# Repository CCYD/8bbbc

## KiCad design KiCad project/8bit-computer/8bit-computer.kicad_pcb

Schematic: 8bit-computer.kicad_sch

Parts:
C1, C3, C5, C6, C7, C8, C9, C10, C11, C12, C13, C14, C15, C16, C17, C18, C19, C20, C21, C22, C23, C24, C25, C26, C27, C28, C29, C30, C31, C32, C33, C34, C35, C36, C37, C38, C39, C40, C41, C42, C43, C44, C45, C46, C47, C48, C51, C52, C53, C54, C55, C56, C57, C60, C61, C63, C64, C65, C66, C67, C68, C69, C70: 0.1uF; C_Disc_D5.0mm_W2.5mm_P5.00mm
C2, C4: 1uF; C_Disc_D5.0mm_W2.5mm_P5.00mm
C49, C50: .01u; C_Disc_D5.0mm_W2.5mm_P5.00mm
C58, C59: 4.7u; CP_Radial_D8.0mm_P2.50mm
C62: 1u; C_Disc_D5.0mm_W2.5mm_P5.00mm
D1, D2, D3, D4, D7, D8, D9, D10, D11, D12, D13, D14, D17, D18, D19, D20, D21, D22, D23, D24, D25, D29, D30, D31, D32, D33, D34, D35, D36, D37, D39, D40, D41, D42, D43, D44, D45, D46, D47, D48, D49, D50, D51, D52, D53, D54, D55, D56, D57, D58, D59, D60, D61, D62, D63, D64, D69, D70, D71, D72, D73, D74, D75, D76, D77, D78, D79, D80, D81, D82, D83, D84, D85, D86, D87, D88, D89, D90, D91, D92, D93: LED; LED_D5.0mm
D5: Green; LED_D5.0mm
D6: Red; LED_D5.0mm
D15: 5817; D_A-405_P7.62mm_Horizontal
D16, D65, D66, D67, D68: Yellow; LED_D5.0mm
D26, D27, D28, D38: LED; LED_D5.0mm; not fitted
H1, H2, H3, H4, H5, H6: MountingHole_Pad; MountingHole_2.7mm_M2.5_DIN965_Pad
IC1, IC2, IC3: AT28C16-15PI; DIP1550W56P254L3190H559Q24N; Mouser Part Number 556-AT28C16-15PI
J1: USB_C_Receptacle_PowerOnly_6P; USB_C_Receptacle_GCT_USB4085
JP1: Jumper_2_Open; PinHeader_1x02_P2.54mm_Vertical
R1, R5, R10, R31, R33, R36, R37, R59, R60, R61, R62, R63, R64, R65, R66, R85, R89, R90, R91, R95, R96: 1K; R_Axial_DIN0207_L6.3mm_D2.5mm_P10.16mm_Horizontal
R2, R3, R4, R9, R16, R17, R35: 10K; R_Axial_DIN0207_L6.3mm_D2.5mm_P10.16mm_Horizontal
R6: 470K; R_Axial_DIN0207_L6.3mm_D2.5mm_P10.16mm_Horizontal
R7, R8: 1M; R_Axial_DIN0207_L6.3mm_D2.5mm_P10.16mm_Horizontal
R15: 120R; R_Axial_DIN0207_L6.3mm_D2.5mm_P10.16mm_Horizontal
R18, R32, R94: R_Axial_DIN0207_L6.3mm_D2.5mm_P10.16mm_Horizontal
R34: R_US; R_Axial_DIN0207_L6.3mm_D2.5mm_P10.16mm_Horizontal
R50: 1K; R_Axial_DIN0207_L6.3mm_D2.5mm_P10.16mm_Horizontal; not fitted
R88: 20K; R_Axial_DIN0207_L6.3mm_D2.5mm_P10.16mm_Horizontal
R92, R93: 5.1K; R_Axial_DIN0207_L6.3mm_D2.5mm_P10.16mm_Horizontal
RN1, RN2, RN3, RN4, RN5, RN6, RN7, RN8, RN9, RN10, RN11: R_Network08_US; R_Array_SIP9
RN12, RN13, RN14, RN15: R_Network04_US; R_Array_SIP5
RV1: 1M; Potentiometer_Alpha_RD901F-40-00D_Single_Vertical_CircularH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
SW1, SW6, SW7: SW_Push; SW_PUSH-12mm
SW2: SW_DIP_x08; DIP-16_W7.62mm_LongPads
SW3: SW_DIP_x04; DIP-8_W7.62mm_LongPads
SW4, SW5, SW9: SW_DPDT_x2_Mine; SW_Push_2P2T_Toggle_CK_PVA2xxH1xxxxxxV2
U1, U2, U3, U52: NE555P; DIP-8_W7.62mm_Socket_LongPads
U4, U12, U13, U30, U31: 74LS04; DIP-14_W7.62mm_Socket_LongPads
U5, U45, U56: 74LS08; DIP-14_W7.62mm_Socket_LongPads
U6: 74LS32; DIP-14_W7.62mm_Socket_LongPads
U7, U25, U26, U35, U36, U37, U39, U46, U57, U58: 74LS173; DIP-16_W7.62mm_Socket_LongPads
U8, U9, U15, U16, U17, U18, U19: 74LS157; DIP-16_W7.62mm_Socket_LongPads
U10, U11: 74F189PC; DIP-16_W7.62mm_Socket_LongPads
U14, U27, U32, U34, U38, U47: 74LS245; DIP-20_W7.62mm_Socket_LongPads
U20, U21: 74LS595; DIP-16_W7.62mm_Socket_LongPads
U22: NodeMCU_v1.0
U23, U24: 74LS00; DIP-14_W7.62mm_Socket_LongPads
U28, U33: 74LS161; DIP-16_W7.62mm_Socket_LongPads
U29: 74LS138; DIP-16_W7.62mm_Socket_LongPads
U40, U41: 74LS283; DIP-16_W7.62mm_Socket_LongPads
U42, U43: 74LS86; DIP-14_W7.62mm_Socket_LongPads
U44: 74LS02; DIP-14_W7.62mm_Socket_LongPads
U48, U49, U50, U51: D168K; D1X8K
U53: 74LS107; DIP-14_W7.62mm_Socket_LongPads
U55: 74LS139; DIP-16_W7.62mm_Socket_LongPads

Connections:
/A: IC3.16 (I/O6), U48.7 (A), U49.7 (A), U50.7 (A), U51.7 (A)
/A0: D26.2 (A), IC1.8 (A0), IC2.8 (A0), U28.14 (Q0), U29.1 (A0)
/A1: D27.2 (A), IC1.7 (A1), IC2.7 (A1), U28.13 (Q1), U29.2 (A1)
/A2: D28.2 (A), IC1.6 (A2), IC2.6 (A2), U28.12 (Q2), U29.3 (A2)
/A4: D22.2 (A), IC1.5 (A3), IC2.5 (A3), U25.3 (Q0)
/A5: D23.2 (A), IC1.4 (A4), IC2.4 (A4), U25.4 (Q1)
/A6: D24.2 (A), IC1.3 (A5), IC2.3 (A5), U25.5 (Q2)
/A7: D25.2 (A), IC1.2 (A6), IC2.2 (A6), U25.6 (Q3)
/B: IC3.15 (I/O5), U48.6 (B), U49.6 (B), U50.6 (B), U51.6 (B)
/BUS_0: D70.2 (A), RN2.2 (R1), U7.14 (D0), U14.18 (B0), U18.2 (I0a), U26.14 (D0), U27.18 (B0), U32.2 (A0), U33.3 (D0), U34.18 (B0), U35.14 (D0), U37.14 (D0), U38.18 (B0), U47.18 (B0), U58.14 (D0)
/BUS_1: D71.2 (A), RN2.3 (R2), U7.13 (D1), U14.17 (B1), U18.5 (I0b), U26.13 (D1), U27.17 (B1), U32.3 (A1), U33.4 (D1), U34.17 (B1), U35.13 (D1), U37.13 (D1), U38.17 (B1), U47.17 (B1), U58.13 (D1)
/BUS_2: D72.2 (A), RN2.4 (R3), U7.12 (D2), U14.16 (B2), U18.11 (I0c), U26.12 (D2), U27.16 (B2), U32.4 (A2), U33.5 (D2), U34.16 (B2), U35.12 (D2), U37.12 (D2), U38.16 (B2), U47.16 (B2), U58.12 (D2)
/BUS_3: D73.2 (A), RN2.5 (R4), U7.11 (D3), U14.15 (B3), U18.14 (I0d), U26.11 (D3), U27.15 (B3), U32.5 (A3), U33.6 (D3), U34.15 (B3), U35.11 (D3), U37.11 (D3), U38.15 (B3), U47.15 (B3), U58.11 (D3)
/BUS_4: D74.2 (A), RN2.6 (R5), U14.14 (B4), U19.2 (I0a), U25.14 (D0), U27.14 (B4), U34.14 (B4), U36.14 (D0), U38.14 (B4), U39.14 (D0), U47.14 (B4), U57.14 (D0)
/BUS_5: D75.2 (A), RN2.7 (R6), U14.13 (B5), U19.5 (I0b), U25.13 (D1), U27.13 (B5), U34.13 (B5), U36.13 (D1), U38.13 (B5), U39.13 (D1), U47.13 (B5), U57.13 (D1)
/BUS_6: D76.2 (A), RN2.8 (R7), U14.12 (B6), U19.11 (I0c), U25.12 (D2), U27.12 (B6), U34.12 (B6), U36.12 (D2), U38.12 (B6), U39.12 (D2), U47.12 (B6), U57.12 (D2)
/BUS_7: D77.2 (A), RN2.9 (R8), U14.11 (B7), U19.14 (I0d), U25.11 (D3), U27.11 (B7), U34.11 (B7), U36.11 (D3), U38.11 (B7), U39.11 (D3), U47.11 (B7), U57.11 (D3)
/C: IC3.14 (I/O4), U48.4 (C), U49.4 (C), U50.4 (C), U51.4 (C)
/CARRY: U41.9 (C4), U46.14 (D0)
/D: IC3.13 (I/O3), U48.2 (D), U49.2 (D), U50.2 (D), U51.2 (D)
/DP: IC3.17 (I/O7), U48.5 (DP), U49.5 (DP), U50.5 (DP), U51.5 (DP)
/E: IC3.11 (I/O2), U48.1 (E), U49.1 (E), U50.1 (E), U51.1 (E)
/F: IC3.9 (I/O0), U48.9 (F), U49.9 (F), U50.9 (F), U51.9 (F)
/G: IC3.10 (I/O1), U48.10 (G), U49.10 (G), U50.10 (G), U51.10 (G)
/IR_A0: D18.2 (A), U26.3 (Q0), U27.2 (A0)
/IR_A1: D19.2 (A), U26.4 (Q1), U27.3 (A1)
/IR_A2: D20.2 (A), U26.5 (Q2), U27.4 (A2)
/IR_A3: D21.2 (A), U26.6 (Q3), U27.5 (A3)
/ZERO: U45.8, U46.13 (D1)
/a0: D65.2 (A), RN13.3 (R2), U9.4 (Za), U10.1 (A0), U11.1 (A0)
/a1: D66.2 (A), RN13.2 (R1), U9.7 (Zb), U10.15 (A1), U11.15 (A1)
/a2: D67.2 (A), RN13.5 (R4), U9.9 (Zc), U10.14 (A2), U11.14 (A2)
/a3: D68.2 (A), RN13.4 (R3), U9.12 (Zd), U10.13 (A3), U11.13 (A3)
/a_d0: D49.2 (A), U34.2 (A0), U35.3 (Q0), U40.5 (A1)
/a_d1: D50.2 (A), U34.3 (A1), U35.4 (Q1), U40.3 (A2)
/a_d2: D51.2 (A), U34.4 (A2), U35.5 (Q2), U40.14 (A3)
/a_d3: D52.2 (A), U34.5 (A3), U35.6 (Q3), U40.12 (A4)
/a_d4: D53.2 (A), U34.6 (A4), U36.3 (Q0), U41.5 (A1)
/a_d5: D54.2 (A), U34.7 (A5), U36.4 (Q1), U41.3 (A2)
/a_d6: D55.2 (A), U34.8 (A6), U36.5 (Q2), U41.14 (A3)
/a_d7: D56.2 (A), U34.9 (A7), U36.6 (Q3), U41.12 (A4)
/b_d0: D57.2 (A), U37.3 (Q0), U38.2 (A0), U42.2
/b_d1: D58.2 (A), U37.4 (Q1), U38.3 (A1), U42.5
/b_d2: D59.2 (A), U37.5 (Q2), U38.4 (A2), U42.10
/b_d3: D60.2 (A), U37.6 (Q3), U38.5 (A3), U42.13
/b_d4: D61.2 (A), U38.6 (A4), U39.3 (Q0), U43.2
/b_d5: D62.2 (A), U38.7 (A5), U39.4 (Q1), U43.5
/b_d6: D63.2 (A), U38.8 (A6), U39.5 (Q2), U43.10
/b_d7: D64.2 (A), U38.9 (A7), U39.6 (Q3), U43.13
/d0: U10.4 (D0), U16.4 (Za)
/d1: U10.6 (D1), U16.7 (Zb)
/d2: U10.10 (D2), U16.9 (Zc)
/d3: U10.12 (D3), U16.12 (Zd)
/d4: U11.4 (D0), U17.4 (Za)
/d5: U11.6 (D1), U17.7 (Zb)
/d6: U11.10 (D2), U17.9 (Zc)
/d7: U11.12 (D3), U17.12 (Zd)
ARD_HALT: R10.2, U6.4, U22.20 (D8)
ARD_MAR_INP_SEL: R31.2, U9.1 (S), U22.22 (D6)
ARD_MA_A0: U9.3 (I1a), U21.3 (QD)
ARD_MA_A1: U9.6 (I1b), U21.2 (QC)
ARD_MA_A2: U9.10 (I1c), U21.1 (QB)
ARD_MA_A3: U9.13 (I1d), U21.15 (QA)
ARD_RAM_D0: U16.3 (I1a), U20.7 (QH)
ARD_RAM_D1: U16.6 (I1b), U20.6 (QG)
ARD_RAM_D2: U16.10 (I1c), U20.5 (QF)
ARD_RAM_D3: U16.13 (I1d), U20.4 (QE)
ARD_RAM_D4: U17.3 (I1a), U20.3 (QD)
ARD_RAM_D5: U17.6 (I1b), U20.2 (QC)
ARD_RAM_D6: U17.10 (I1c), U20.1 (QB)
ARD_RAM_D7: U17.13 (I1d), U20.15 (QA)
ARD_RAM_INP_SEL: D16.2 (A), R34.2, U16.1 (S), U17.1 (S), U22.21 (D7)
ARD_RAM_WR_EN: R18.1, U10.3 (*WE), U11.3 (*WE), U15.12 (Zd), U22.27 (D3)
ARD_RESET: R36.1, SW7.2, U22.23 (D5), U23.12, U23.13
CLK: D4.2 (A), U4.13, U5.8, U7.7 (Cp), U24.12, U24.13, U25.7 (Cp), U26.7 (Cp), U33.2 (CP), U35.7 (Cp), U36.7 (Cp), U37.7 (Cp), U39.7 (Cp), U46.7 (Cp), U56.1
GND: C1.2, C2.2, C3.2, C4.2, C5.2, C6.2, C7.1, C8.1, C9.1, C10.1, C11.1, C12.1, C13.1, C14.1, C15.1, C16.1, C17.1, C18.1, C19.1, C21.1, C22.1, C23.1, C24.1, C25.1, C26.1, C27.1, C28.1, C29.1, C30.1, C31.1, C32.2, C33.2, C34.1, C35.1, C36.1, C37.1, C38.1, C39.1, C40.1, C41.1, C42.1, C43.1, C44.1, C45.1, C46.1, C47.1, C48.1, C49.2, C50.2, C51.1, C52.2, C53.2, C54.1, C55.1, C56.1, C57.2, C58.2, C59.2, C60.1, C61.2, C62.2, C63.1, C64.1, C65.1, C66.1, C67.1, C68.1, C69.1, C70.1, H1.1, H2.1, H3.1, H4.1, H5.1, H6.1, IC1.1 (A7), IC1.12 (GND), IC1.18 (~CE), IC1.19 (A10), IC1.20 (~OE), IC2.12 (GND), IC2.18 (~CE), IC2.19 (A10), IC2.20 (~OE), IC3.12 (GND), IC3.18 (~CE), IC3.20 (~OE), J1.A12 (GND), J1.B12 (GND), J1.S1 (SHIELD), R2.2, R3.2, R4.1, R9.2, R10.1, R31.1, R33.2, R34.1, R35.2, R36.2, R37.2, R50.2, R65.2, R66.2, R89.2, R92.1, R93.1, R94.1, R95.2, RN2.1 (common), RN3.1 (common), RN4.1 (common), RN5.1 (common), RN6.1 (common), RN7.1 (common), RN8.1 (common), RN9.1 (common), RN10.1 (common), RN11.1 (common), RN13.1 (common), RN14.1 (common), RN15.1 (common), RV1.MP (MountPin), SW1.1, SW2.1, SW2.2, SW2.3, SW2.4, SW2.5, SW2.6, SW2.7, SW2.8, SW3.1, SW3.2, SW3.3, SW3.4, SW4.1 (A), SW5.1 (A), SW6.1, SW9.2 (C), U1.1 (GND), U2.1 (GND), U3.1 (GND), U3.6 (THR), U4.7 (GND), U5.7 (GND), U6.7 (GND), U7.1 (Oe1), U7.2 (Oe2), U7.8 (GND), U8.8 (GND), U8.15 (E), U9.8 (GND), U9.15 (E), U10.2 (*CS), U10.8 (GND), U11.2 (*CS), U11.8 (GND), U12.7 (GND), U13.7 (GND), U14.10 (GND), U15.8 (GND), U15.15 (E), U16.8 (GND), U16.15 (E), U17.8 (GND), U17.15 (E), U18.8 (GND), U18.15 (E), U19.8 (GND), U19.15 (E), U20.8 (GND), U21.8 (GND), U22.10 (GND), U22.14 (GND), U22.17 (GND), U22.24 (GND), U23.7 (GND), U24.7 (GND), U25.1 (Oe1), U25.2 (Oe2), U25.8 (GND), U26.1 (Oe1), U26.2 (Oe2), U26.8 (GND), U27.6 (A4), U27.7 (A5), U27.8 (A6), U27.9 (A7), U27.10 (GND), U28.8 (GND), U29.4 (E1), U29.5 (E2), U29.8 (GND), U30.7 (GND), U31.7 (GND), U32.1 (A->B), U32.10 (GND), U33.8 (GND), U34.10 (GND), U35.1 (Oe1), U35.2 (Oe2), U35.8 (GND), U36.1 (Oe1), U36.2 (Oe2), U36.8 (GND), U37.1 (Oe1), U37.2 (Oe2), U37.8 (GND), U38.10 (GND), U39.1 (Oe1), U39.2 (Oe2), U39.8 (GND), U40.8 (GND), U41.8 (GND), U42.7 (GND), U43.7 (GND), U44.7 (GND), U45.7 (GND), U46.1 (Oe1), U46.2 (Oe2), U46.8 (GND), U46.11 (D3), U46.12 (D2), U47.10 (GND), U52.1 (GND), U53.7 (GND), U55.1 (E), U55.8 (GND), U56.7 (GND), U57.1 (Oe1), U57.2 (Oe2), U57.8 (GND), U57.9 (E1), U57.10 (E2), U58.1 (Oe1), U58.2 (Oe2), U58.8 (GND), U58.9 (E1), U58.10 (E2)
HALT: D78.2 (A), IC1.17 (I/O7), U6.5
JC_FLAG: D47.2 (A), IC1.23 (A8), IC2.23 (A8), U46.3 (Q0)
JZ_FLAG: D48.2 (A), IC1.22 (A9), IC2.22 (A9), U46.4 (Q1)
unnamed: C20.1, R37.1, U24.1
unnamed: C20.2, U24.8
unnamed: D1.2 (A), U1.3 (Q), U5.2
unnamed: D1.1 (K), R2.1
unnamed: D2.2 (A), U2.3 (Q), U5.5
unnamed: D2.1 (K), R3.1
unnamed: D3.2 (A), R8.2, U3.3 (Q), U4.1, U5.1
unnamed: D3.1 (K), R4.2
unnamed: D4.1 (K), R9.1
unnamed: D5.2 (A), R16.2
unnamed: D5.1 (K), SW4.3 (B)
unnamed: D6.2 (A), R17.2
unnamed: D6.1 (K), R15.2, SW4.2 (C), U8.1 (S), U15.1 (S), U24.4, U24.5
unnamed: D7.2 (A), U12.2, U14.2 (A0)
unnamed: D7.1 (K), RN5.2 (R1)
unnamed: D8.2 (A), U12.4, U14.3 (A1)
unnamed: D8.1 (K), RN5.3 (R2)
unnamed: D9.2 (A), U12.6, U14.4 (A2)
unnamed: D9.1 (K), RN5.4 (R3)
unnamed: D10.2 (A), U12.8, U14.5 (A3)
unnamed: D10.1 (K), RN5.5 (R4)
unnamed: D11.2 (A), U12.10, U14.6 (A4)
unnamed: D11.1 (K), RN5.6 (R5)
unnamed: D12.2 (A), U12.12, U14.7 (A5)
unnamed: D12.1 (K), RN5.7 (R6)
unnamed: D13.2 (A), U13.2, U14.8 (A6)
unnamed: D13.1 (K), RN5.8 (R7)
unnamed: D14.2 (A), U13.4, U14.9 (A7)
unnamed: D14.1 (K), RN5.9 (R8)
unnamed: D15.1 (K), U22.15 (VIN)
unnamed: D16.1 (K), R33.1
unnamed: D17.2 (A), U4.9, U6.6
unnamed: D17.1 (K), R35.1
unnamed: D18.1 (K), RN3.2 (R1)
unnamed: D19.1 (K), RN3.3 (R2)
unnamed: D20.1 (K), RN3.4 (R3)
unnamed: D21.1 (K), RN3.5 (R4)
unnamed: D22.1 (K), RN3.6 (R5)
unnamed: D23.1 (K), RN3.7 (R6)
unnamed: D24.1 (K), RN3.8 (R7)
unnamed: D25.1 (K), RN3.9 (R8)
unnamed: D26.1 (K), RN11.9 (R8)
unnamed: D27.1 (K), RN11.8 (R7)
unnamed: D28.1 (K), RN11.7 (R6)
unnamed: D29.2 (A), U29.15 (O0)
unnamed: D29.1 (K), RN11.2 (R1)
unnamed: D30.2 (A), U29.14 (O1)
unnamed: D30.1 (K), RN11.3 (R2)
unnamed: D31.2 (A), U29.13 (O2)
unnamed: D31.1 (K), RN11.4 (R3)
unnamed: D32.2 (A), U29.12 (O3)
unnamed: D32.1 (K), RN11.5 (R4)
unnamed: D33.2 (A), U29.11 (O4)
unnamed: D33.1 (K), RN11.6 (R5)
unnamed: D34.2 (A), U32.18 (B0), U33.14 (Q0)
unnamed: D34.1 (K), RN15.2 (R1)
unnamed: D35.2 (A), U32.17 (B1), U33.13 (Q1)
unnamed: D35.1 (K), RN15.3 (R2)
unnamed: D36.2 (A), U32.16 (B2), U33.12 (Q2)
unnamed: D36.1 (K), RN15.4 (R3)
unnamed: D37.2 (A), U32.15 (B3), U33.11 (Q3)
unnamed: D37.1 (K), RN15.5 (R4)
unnamed: D38.2 (A), U22.4 (SD3)
unnamed: D38.1 (K), R50.1
unnamed: D39.2 (A), U40.4 (S1), U44.12, U47.2 (A0)
unnamed: D39.1 (K), RN6.2 (R1)
unnamed: D40.2 (A), U40.1 (S2), U44.11, U47.3 (A1)
unnamed: D40.1 (K), RN6.3 (R2)
unnamed: D41.2 (A), U40.13 (S3), U44.9, U47.4 (A2)
unnamed: D41.1 (K), RN6.4 (R3)
unnamed: D42.2 (A), U40.10 (S4), U44.8, U47.5 (A3)
unnamed: D42.1 (K), RN6.5 (R4)
unnamed: D43.2 (A), U41.4 (S1), U44.6, U47.6 (A4)
unnamed: D43.1 (K), RN6.6 (R5)
unnamed: D44.2 (A), U41.1 (S2), U44.5, U47.7 (A5)
unnamed: D44.1 (K), RN6.7 (R6)
unnamed: D45.2 (A), U41.13 (S3), U44.3, U47.8 (A6)
unnamed: D45.1 (K), RN6.8 (R7)
unnamed: D46.2 (A), U41.10 (S4), U44.2, U47.9 (A7)
unnamed: D46.1 (K), RN6.9 (R8)
unnamed: D47.1 (K), R65.1
unnamed: D48.1 (K), R66.1
unnamed: D49.1 (K), RN8.2 (R1)
unnamed: D50.1 (K), RN8.3 (R2)
unnamed: D51.1 (K), RN8.4 (R3)
unnamed: D52.1 (K), RN8.5 (R4)
unnamed: D53.1 (K), RN8.6 (R5)
unnamed: D54.1 (K), RN8.7 (R6)
unnamed: D55.1 (K), RN8.8 (R7)
unnamed: D56.1 (K), RN8.9 (R8)
unnamed: D57.1 (K), RN7.2 (R1)
unnamed: D58.1 (K), RN7.3 (R2)
unnamed: D59.1 (K), RN7.4 (R3)
unnamed: D60.1 (K), RN7.5 (R4)
unnamed: D61.1 (K), RN7.6 (R5)
unnamed: D62.1 (K), RN7.7 (R6)
unnamed: D63.1 (K), RN7.8 (R7)
unnamed: D64.1 (K), RN7.9 (R8)
unnamed: D65.1 (K), RN14.5 (R4)
unnamed: D66.1 (K), RN14.4 (R3)
unnamed: D67.1 (K), RN14.3 (R2)
unnamed: D68.1 (K), RN14.2 (R1)
unnamed: D69.1 (K), R94.2
unnamed: D70.1 (K), RN4.2 (R1)
unnamed: D71.1 (K), RN4.3 (R2)
unnamed: D72.1 (K), RN4.4 (R3)
unnamed: D73.1 (K), RN4.5 (R4)
unnamed: D74.1 (K), RN4.6 (R5)
unnamed: D75.1 (K), RN4.7 (R6)
unnamed: D76.1 (K), RN4.8 (R7)
unnamed: D77.1 (K), RN4.9 (R8)
unnamed: D78.1 (K), RN9.2 (R1)
unnamed: D79.2 (A), IC1.16 (I/O6), U30.1
unnamed: D79.1 (K), RN9.3 (R2)
unnamed: D80.1 (K), RN9.4 (R3)
unnamed: D81.2 (A), IC1.14 (I/O4), U30.3
unnamed: D81.1 (K), RN9.5 (R4)
unnamed: D82.2 (A), IC1.13 (I/O3), U30.5
unnamed: D82.1 (K), RN9.6 (R5)
unnamed: D83.2 (A), IC1.11 (I/O2), U30.13
unnamed: D83.1 (K), RN9.7 (R6)
unnamed: D84.2 (A), IC1.9 (I/O0), U30.9
unnamed: D84.1 (K), RN9.8 (R7)
unnamed: D85.2 (A), IC1.10 (I/O1), U30.11
unnamed: D85.1 (K), RN9.9 (R8)
unnamed: D86.2 (A), IC2.17 (I/O7), U31.1
unnamed: D86.1 (K), RN10.2 (R1)
unnamed: D87.1 (K), RN10.3 (R2)
unnamed: D88.2 (A), IC2.15 (I/O5), U31.3
unnamed: D88.1 (K), RN10.4 (R3)
unnamed: D89.1 (K), RN10.5 (R4)
unnamed: D90.2 (A), IC2.11 (I/O2), U31.13
unnamed: D90.1 (K), RN10.6 (R5)
unnamed: D91.1 (K), RN10.7 (R6)
unnamed: D92.2 (A), IC2.10 (I/O1), U31.11
unnamed: D92.1 (K), RN10.8 (R7)
unnamed: D93.2 (A), IC2.9 (I/O0), U31.5
unnamed: D93.1 (K), RN10.9 (R8)
unnamed: IC3.8 (A0), U58.3 (Q0)
unnamed: IC3.7 (A1), U58.4 (Q1)
unnamed: IC3.6 (A2), U58.5 (Q2)
unnamed: IC3.5 (A3), U58.6 (Q3)
unnamed: IC3.4 (A4), U57.3 (Q0)
unnamed: IC3.3 (A5), U57.4 (Q1)
unnamed: IC3.2 (A6), U57.5 (Q2)
unnamed: IC3.1 (A7), U57.6 (Q3)
unnamed: IC3.23 (A8), U53.2 (~Q), U53.9 (C), U55.2 (A0)
unnamed: IC3.22 (A9), U53.5 (Q), U55.3 (A1)
unnamed: IC3.19 (A10), JP1.1 (A), R89.1
unnamed: J1.A5 (CC1), R93.2
unnamed: J1.B5 (CC2), R92.2
unnamed: R59.1, U45.12, U45.13
unnamed: R60.2, U5.12, U5.13
unnamed: R61.2, U4.3, U4.5, U4.11
unnamed: R62.2, U6.9, U6.10, U6.12, U6.13
unnamed: R63.1, U13.5, U13.9, U13.11, U13.13
unnamed: R64.1, U31.9
unnamed: R91.1, U56.4, U56.5, U56.9, U56.10, U56.12, U56.13
unnamed: R96.2, RV1.3
unnamed: RN1.2 (R1), SW2.16, U18.3 (I1a)
unnamed: RN1.3 (R2), SW2.15, U18.6 (I1b)
unnamed: RN1.4 (R3), SW2.14, U18.10 (I1c)
unnamed: RN1.5 (R4), SW2.13, U18.13 (I1d)
unnamed: RN1.6 (R5), SW2.12, U19.3 (I1a)
unnamed: RN1.7 (R6), SW2.11, U19.6 (I1b)
unnamed: RN1.8 (R7), SW2.10, U19.10 (I1c)
unnamed: RN1.9 (R8), SW2.9, U19.13 (I1d)
unnamed: RN12.2 (R1), SW3.8, U8.11 (I0c)
unnamed: RN12.3 (R2), SW3.7, U8.14 (I0d)
unnamed: RN12.4 (R3), SW3.6, U8.5 (I0b)
unnamed: RN12.5 (R4), SW3.5, U8.2 (I0a)
unnamed: SW5.3 (B), U3.4 (R)
unnamed: R7.2, SW5.2 (C), U3.2 (TR)
unnamed: SW9.3 (B), U22.26 (D4)
unnamed: C1.1, U1.5 (CV)
unnamed: R1.1, R96.1, U1.7 (DIS)
unnamed: C2.1, RV1.2, U1.2 (TR), U1.6 (THR)
unnamed: C3.1, U2.5 (CV)
unnamed: C4.1, R6.2, U2.6 (THR), U2.7 (DIS)
unnamed: C6.1, R5.2, SW1.2, U2.2 (TR)
unnamed: C5.1, U3.5 (CV)
unnamed: U4.2, U5.4
unnamed: U4.8, U5.10
unnamed: U5.3, U6.1
unnamed: U5.6, U6.2
unnamed: U5.9, U6.3
unnamed: U7.3 (Q0), U8.3 (I1a)
unnamed: U7.4 (Q1), U8.6 (I1b)
unnamed: U7.5 (Q2), U8.10 (I1c)
unnamed: U7.6 (Q3), U8.13 (I1d)
unnamed: U8.4 (Za), U9.2 (I0a)
unnamed: U8.7 (Zb), U9.5 (I0b)
unnamed: U8.9 (Zc), U9.11 (I0c)
unnamed: U8.12 (Zd), U9.14 (I0d)
unnamed: U10.5 (*O0), U12.1
unnamed: U10.7 (*O1), U12.3
unnamed: U10.9 (*O2), U12.5
unnamed: U10.11 (*O3), U12.9
unnamed: U11.5 (*O0), U12.11
unnamed: U11.7 (*O1), U12.13
unnamed: U11.9 (*O2), U13.1
unnamed: U11.11 (*O3), U13.3
unnamed: C13.2, R32.2, SW6.2, U15.14 (I0d)
unnamed: U15.13 (I1d), U24.3
unnamed: U16.2 (I0a), U18.4 (Za)
unnamed: U16.5 (I0b), U18.7 (Zb)
unnamed: U16.11 (I0c), U18.9 (Zc)
unnamed: U16.14 (I0d), U18.12 (Zd)
unnamed: U17.2 (I0a), U19.4 (Za)
unnamed: U17.5 (I0b), U19.7 (Zb)
unnamed: U17.11 (I0c), U19.9 (Zc)
unnamed: U17.14 (I0d), U19.12 (Zd)
unnamed: U18.1 (S), U19.1 (S), U24.6
unnamed: U20.9 (QH'), U21.14 (SER)
unnamed: C62.1, U20.12 (RCLK), U21.12 (RCLK), U22.29 (D1)
unnamed: U20.14 (SER), U22.30 (D0)
unnamed: U20.11 (SRCLK), U21.11 (SRCLK), U22.28 (D2)
unnamed: R95.1, U20.13 (~OE), U21.13 (~OE)
unnamed: U23.3, U23.4, U23.5
unnamed: U24.9, U24.10, U24.11
unnamed: U23.6, U28.1 (~MR)
unnamed: U23.2, U29.10 (O5)
unnamed: U40.6 (B1), U42.3
unnamed: U40.2 (B2), U42.6
unnamed: U40.15 (B3), U42.8
unnamed: U40.11 (B4), U42.11
unnamed: U40.9 (C4), U41.7 (C0)
unnamed: U41.6 (B1), U43.3
unnamed: U41.2 (B2), U43.6
unnamed: U41.15 (B3), U43.8
unnamed: U41.11 (B4), U43.11
unnamed: U44.1, U45.1
unnamed: U44.4, U45.2
unnamed: U44.10, U45.4
unnamed: U44.13, U45.5
unnamed: U45.3, U45.9
unnamed: U45.6, U45.10
unnamed: C50.1, U52.5 (CV)
unnamed: R85.2, R88.2, U52.7 (DIS)
unnamed: U52.3 (Q), U53.12 (C)
unnamed: C49.1, R88.1, U52.2 (TR), U52.6 (THR)
unnamed: U48.3 (CC), U48.8 (CC), U55.4 (O0)
unnamed: U49.3 (CC), U49.8 (CC), U55.5 (O1)
unnamed: U50.3 (CC), U50.8 (CC), U55.6 (O2)
unnamed: U51.3 (CC), U51.8 (CC), U55.7 (O3)
unnamed: R90.2, U55.13 (A1), U55.14 (A0)
unnamed: U56.3, U57.7 (Cp), U58.7 (Cp)
OUTPUT_IN: D89.2 (A), IC2.14 (I/O4), U56.2
PC_EN: D91.2 (A), IC2.13 (I/O3), U33.7 (CEP), U33.10 (CET)
RAM_IN: D80.2 (A), IC1.15 (I/O5), U24.2
RESET: U7.15 (Mr), U23.8, U25.15 (Mr), U26.15 (Mr), U35.15 (Mr), U36.15 (Mr), U37.15 (Mr), U39.15 (Mr), U46.15 (Mr), U57.15 (Mr), U58.15 (Mr)
SUBTRACT: D87.2 (A), IC2.16 (I/O6), U40.7 (C0), U42.1, U42.4, U42.9, U42.12, U43.1, U43.4, U43.9, U43.12
VCC: C7.2, C8.2, C9.2, C10.2, C11.2, C12.2, C14.2, C15.2, C16.2, C17.2, C18.2, C19.2, C21.2, C22.2, C23.2, C24.2, C25.2, C26.2, C27.2, C28.2, C29.2, C30.2, C31.2, C32.1, C33.1, C34.2, C35.2, C36.2, C37.2, C38.2, C39.2, C40.2, C41.2, C42.2, C43.2, C44.2, C45.2, C46.2, C47.2, C48.2, C51.2, C52.1, C53.1, C54.2, C55.2, C56.2, C57.1, C58.1, C59.1, C60.2, C61.1, C63.2, C64.2, C65.2, C66.2, C67.2, C68.2, C69.2, C70.2, D15.2 (A), D69.2 (A), IC1.21 (~WE), IC1.24 (VCC), IC2.1 (A7), IC2.21 (~WE), IC2.24 (VCC), IC3.21 (~WE), IC3.24 (VCC), J1.A9 (VBUS), J1.B9 (VBUS), JP1.2 (B), R1.2, R5.1, R6.1, R7.1, R8.1, R15.1, R16.1, R17.1, R18.2, R32.1, R59.2, R60.1, R61.1, R62.1, R63.2, R64.2, R85.1, R90.1, R91.2, RN1.1 (common), RN12.1 (common), SW7.1, SW9.1 (A), U1.8 (VCC), U2.8 (VCC), U3.8 (VCC), U4.14 (VCC), U5.14 (VCC), U6.14 (VCC), U7.16 (VCC), U8.16 (VCC), U9.16 (VCC), U10.16 (VCC), U11.16 (VCC), U12.14 (VCC), U13.14 (VCC), U14.1 (A->B), U14.20 (VCC), U15.2 (I0a), U15.3 (I1a), U15.5 (I0b), U15.6 (I1b), U15.10 (I1c), U15.11 (I0c), U15.16 (VCC), U16.16 (VCC), U17.16 (VCC), U18.16 (VCC), U19.16 (VCC), U20.10 (~SRCLR), U20.16 (VCC), U21.10 (~SRCLR), U21.16 (VCC), U23.14 (VCC), U24.14 (VCC), U25.16 (VCC), U26.16 (VCC), U27.1 (A->B), U27.20 (VCC), U28.3 (D0), U28.4 (D1), U28.5 (D2), U28.6 (D3), U28.7 (CEP), U28.9 (~PE), U28.16 (VCC), U29.6 (E3), U29.16 (VCC), U30.14 (VCC), U31.14 (VCC), U32.20 (VCC), U33.16 (VCC), U34.1 (A->B), U34.20 (VCC), U35.16 (VCC), U36.16 (VCC), U37.16 (VCC), U38.1 (A->B), U38.19 (CE), U38.20 (VCC), U39.16 (VCC), U40.16 (VCC), U41.16 (VCC), U42.14 (VCC), U43.14 (VCC), U44.14 (VCC), U45.14 (VCC), U46.16 (VCC), U47.1 (A->B), U47.20 (VCC), U52.8 (VCC), U53.1 (J), U53.4 (K), U53.8 (J), U53.10 (~R), U53.11 (K), U53.13 (~R), U53.14 (VCC), U55.15 (E), U55.16 (VCC), U56.14 (VCC), U57.16 (VCC), U58.16 (VCC)
~A_REG_IN: U30.8, U35.9 (E1), U35.10 (E2), U36.9 (E1), U36.10 (E2)
~A_REG_OUT: U30.10, U34.19 (CE)
~B_REG_IN: U31.4, U37.9 (E1), U37.10 (E2), U39.9 (E1), U39.10 (E2)
~CLK: U4.12, U28.2 (CP)
~FLAG_IN: U31.6, U46.9 (E1), U46.10 (E2)
~IR_IN: U25.9 (E1), U25.10 (E2), U26.9 (E1), U26.10 (E2), U30.12
~IR_OUT: U27.19 (CE), U30.6
~JUMP: U31.10, U33.9 (~PE)
~MAR_IN: U7.9 (E1), U7.10 (E2), U30.2
~PC_OUT: U31.12, U32.19 (CE)
~RAM_OUT: U14.19 (CE), U30.4
~RESET: U23.1, U23.9, U23.10, U23.11, U33.1 (~MR)
~SUM_OUT: U31.2, U47.19 (CE)

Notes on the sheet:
RESISTORS FOR LEDS: RED: 1K GREEN: 4.7k BLUE: 1K YELLOW: 470k Swap 1K for 4.7K if too bright.
NOTE: D0 is LSB . . D7 is MSB
Memory and Memory Address Register
Step - Binary
Reset Circuit
Instruction - Decimal (visually)
Right (Ard)
Extra Register
A/B Registers and Arithmetic Logic Unit
Control Logic
Program Counter
Clock Module
Instruction
TODO: Review this switch
Left (Switches)
Set ESP Wifi Mode (Station vs AP Mode)
TODO: reorganize address and data lines according to bus
1K resistors probably? Had an issue with the HALT voltage dropping too low.
Wifi Mode Indicator

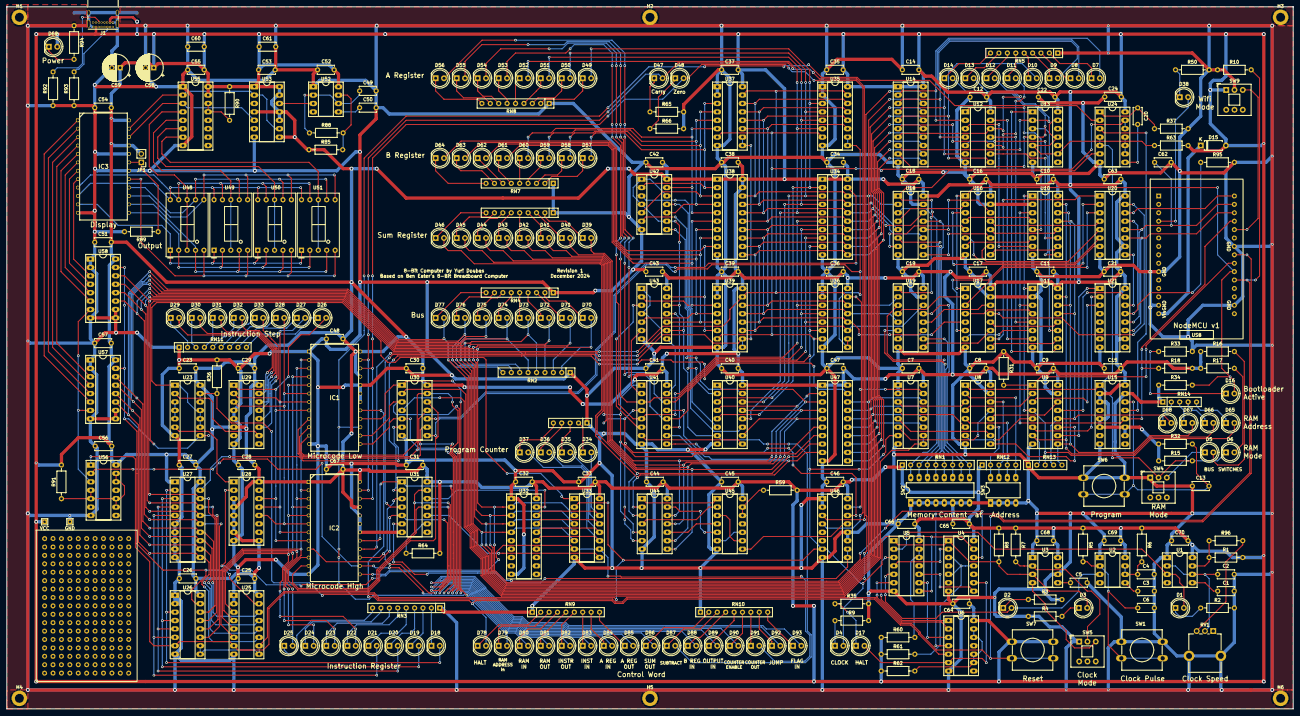
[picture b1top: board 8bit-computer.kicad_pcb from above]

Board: 4 copper layers, 388.6 x 212.1 mm, 295 parts (0 on the bottom side), 345 nets.

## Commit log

2023-04-30 Add files via upload
    Instruction set
2024-12-27 Microcode build tool
2024-12-27 Added KiCad Project
